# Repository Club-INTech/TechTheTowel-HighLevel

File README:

INTech  2015-2016
In GIT we trust.

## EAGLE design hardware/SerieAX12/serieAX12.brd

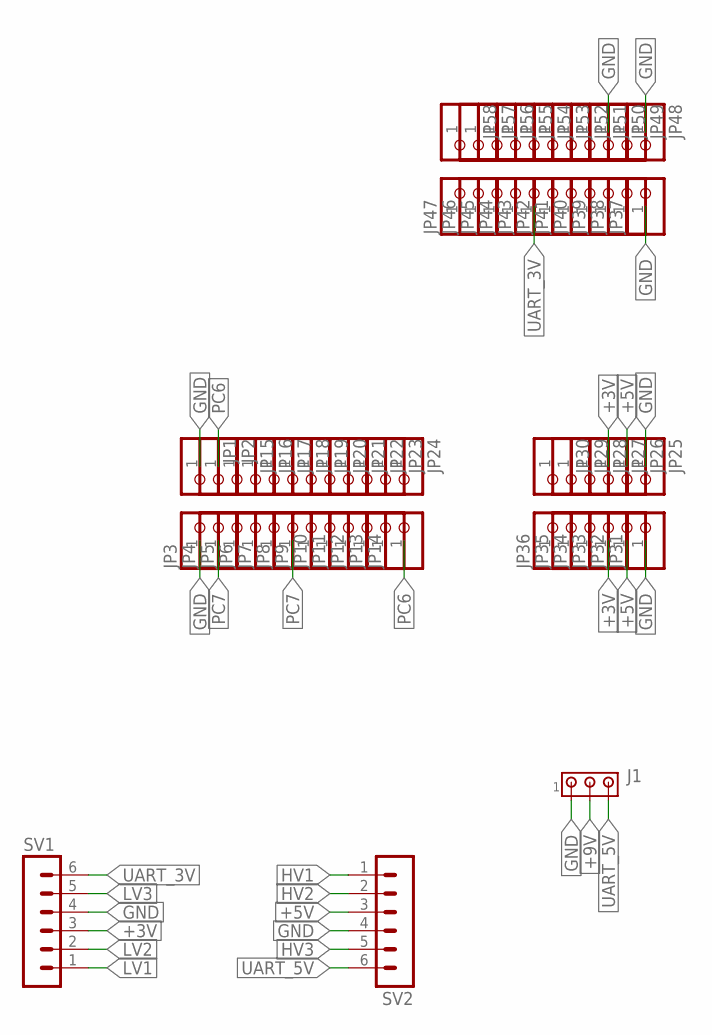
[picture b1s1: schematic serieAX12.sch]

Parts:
J1: MTA03-100; 10X03MTA
JP1, JP2, JP3, JP4, JP5, JP6, JP7, JP8, JP9, JP10, JP11, JP12, JP13, JP14, JP15, JP16, JP17, JP18, JP19, JP20, JP21, JP22, JP23, JP24, JP25, JP26, JP27, JP28, JP29, JP30, JP31, JP32, JP33, JP34, JP35, JP36, JP37, JP38, JP39, JP40, JP41, JP42, JP43, JP44, JP45, JP46, JP47, JP48, JP49, JP50, JP51, JP52, JP53, JP54, JP55, JP56, JP57, JP58: PINHD-1X1; 1X01
SV1, SV2: MA06-1

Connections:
+3V: JP27.1, JP33.1, SV1.3
+5V: JP26.1, JP32.1, SV2.3
+9V: J1.2
GND: J1.1, JP1.1, JP3.1, JP25.1, JP31.1, JP37.1, JP48.1, JP50.1, SV1.4, SV2.4
HV1: SV2.1
HV2: SV2.2
HV3: SV2.5
LV1: SV1.1
LV2: SV1.2
LV3: SV1.5
PC6: JP2.1, JP14.1
PC7: JP4.1, JP8.1
UART_3V: JP43.1, SV1.6
UART_5V: J1.3, SV2.6

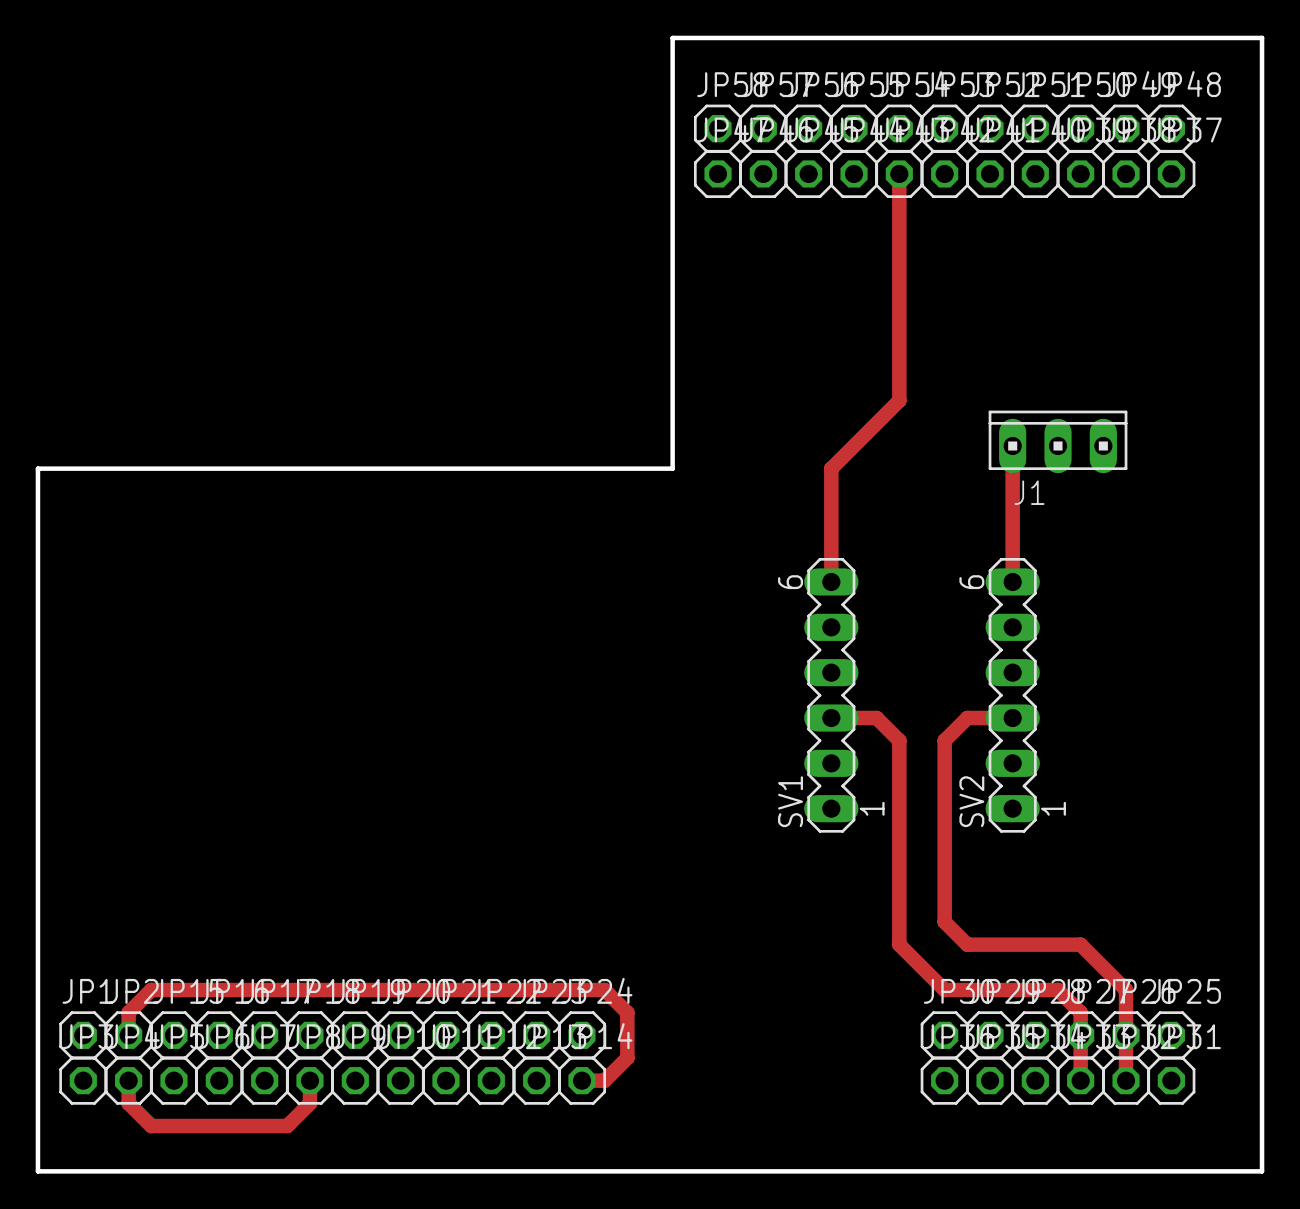
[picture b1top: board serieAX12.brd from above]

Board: 2 copper layers, 68.6 x 63.5 mm, 61 parts (0 on the bottom side), 7 nets.

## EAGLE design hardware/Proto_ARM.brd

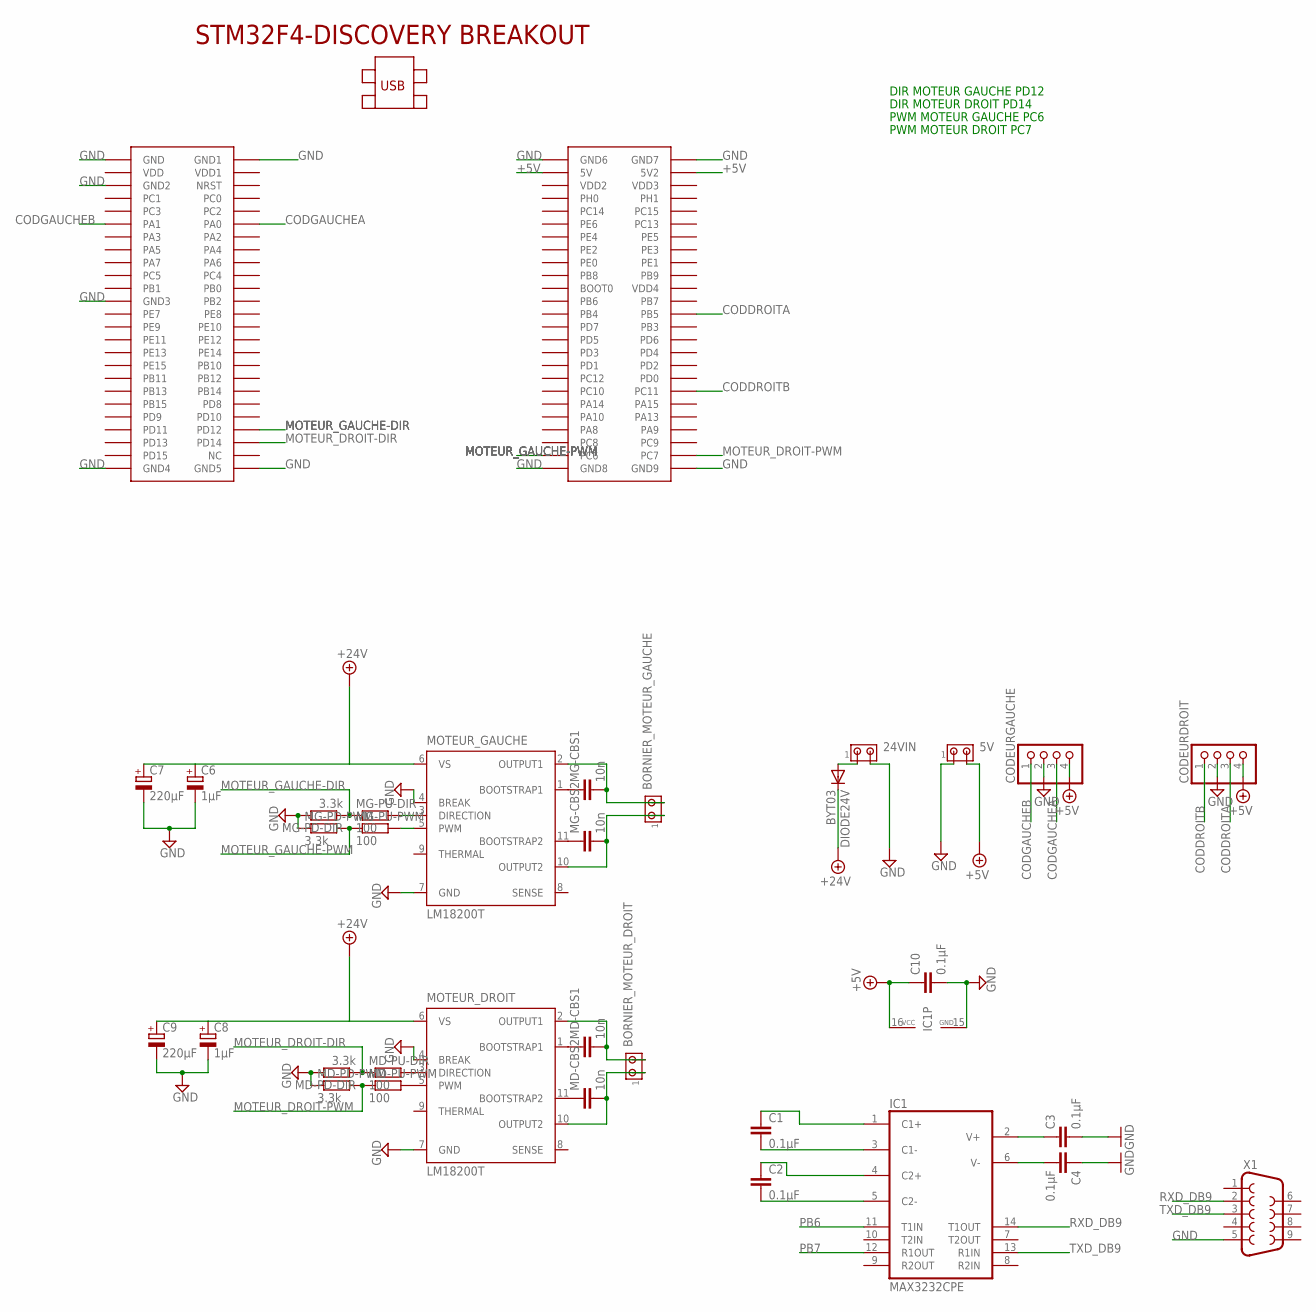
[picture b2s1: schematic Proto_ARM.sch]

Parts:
5V, 24VIN: MTA02-156; 1X2MTA
BORNIER_MOTEUR_DROIT: MTA02-156; 1X2MTA
BORNIER_MOTEUR_GAUCHE: MTA02-156; 1X2MTA
C1, C2, C3, C4, C10: 0.1µF; C050-035X075
C6, C8: 1µF; E3,5-8
C7, C9: 220µF; E3,5-8
CODEURDROIT: PINHD-1X4; 1X04
CODEURGAUCHE: PINHD-1X4; 1X04
DIODE24V: BYT03; DO27-15
IC1: MAX3232CPE; DIL16; MPN MAX3232CPE+
MD-CBS1, MD-CBS2: 10n; C050-025X075
MD-PD-DIR: 3.3k; 0207/7
MD-PD-PWM: 3.3k; 0207/7
MD-PU-DIR: 100; 0207/7
MD-PU-PWM: 100; 0207/7
MG-CBS1, MG-CBS2: 10n; C050-025X075
MG-PD-DIR: 3.3k; 0207/7
MG-PD-PWM: 3.3k; 0207/7
MG-PU-DIR: 100; 0207/7
MG-PU-PWM: 100; 0207/7
MOTEUR_DROIT: LM18200T; TO-220-11
MOTEUR_GAUCHE: LM18200T; TO-220-11
U$1: STM32F4-DISCOVERY
X1: F09HP

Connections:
+5V: 5V.2, C10.1, CODEURDROIT.4, CODEURGAUCHE.4, IC1.16 (VCC), U$1.P$53 (5V), U$1.P$54 (5V2)
+24V: C6.+, C7.+, C8.+, C9.+, DIODE24V.C, MOTEUR_DROIT.6 (VS), MOTEUR_GAUCHE.6 (VS)
CODDROITA: CODEURDROIT.3, U$1.P$76 (PB5)
CODDROITB: CODEURDROIT.1, U$1.P$88 (PC11)
CODGAUCHEA: CODEURGAUCHE.3, U$1.P$12 (PA0)
CODGAUCHEB: CODEURGAUCHE.1, U$1.P$11 (PA1)
GND: 5V.1, 24VIN.2, C3.2, C4.1, C6.-, C7.-, C8.-, C9.-, C10.2, CODEURDROIT.2, CODEURGAUCHE.2, IC1.15 (GND), MD-PD-DIR.2, MD-PD-PWM.1, MG-PD-DIR.2, MG-PD-PWM.1, MOTEUR_DROIT.4 (BREAK), MOTEUR_DROIT.7 (GND), MOTEUR_GAUCHE.4 (BREAK), MOTEUR_GAUCHE.7 (GND), U$1.P$1 (GND), U$1.P$2 (GND1), U$1.P$5 (GND2), U$1.P$23 (GND3), U$1.P$49 (GND4), U$1.P$50 (GND5), U$1.P$51 (GND6), U$1.P$52 (GND7), U$1.P$99 (GND8), U$1.P$100 (GND9), X1.5
MOTEUR_DROIT-DIR: MD-PD-DIR.1, MD-PU-DIR.1, U$1.P$46 (PD14)
MOTEUR_DROIT-PWM: MD-PD-PWM.2, MD-PU-PWM.1, U$1.P$98 (PC7)
MOTEUR_GAUCHE-DIR: MG-PD-DIR.1, MG-PU-DIR.1, U$1.P$44 (PD12)
MOTEUR_GAUCHE-PWM: MG-PD-PWM.2, MG-PU-PWM.1, U$1.P$97 (PC6)
unnamed: C1.1, IC1.1 (C1+)
unnamed: MG-CBS1.1, MOTEUR_GAUCHE.1 (BOOTSTRAP1)
unnamed: MG-CBS2.1, MOTEUR_GAUCHE.11 (BOOTSTRAP2)
unnamed: MD-CBS2.1, MOTEUR_DROIT.11 (BOOTSTRAP2)
unnamed: MD-CBS1.1, MOTEUR_DROIT.1 (BOOTSTRAP1)
unnamed: BORNIER_MOTEUR_DROIT.2, MD-CBS1.2, MOTEUR_DROIT.2 (OUTPUT1)
unnamed: BORNIER_MOTEUR_DROIT.1, MD-CBS2.2, MOTEUR_DROIT.10 (OUTPUT2)
unnamed: BORNIER_MOTEUR_GAUCHE.1, MG-CBS2.2, MOTEUR_GAUCHE.10 (OUTPUT2)
unnamed: BORNIER_MOTEUR_GAUCHE.2, MG-CBS1.2, MOTEUR_GAUCHE.2 (OUTPUT1)
unnamed: C4.2, IC1.6 (V-)
unnamed: MG-PU-DIR.2, MOTEUR_GAUCHE.3 (DIRECTION)
unnamed: MG-PU-PWM.2, MOTEUR_GAUCHE.5 (PWM)
unnamed: MD-PU-DIR.2, MOTEUR_DROIT.3 (DIRECTION)
unnamed: MD-PU-PWM.2, MOTEUR_DROIT.5 (PWM)
unnamed: C3.1, IC1.2 (V+)
unnamed: C1.2, IC1.3 (C1-)
unnamed: 24VIN.1, DIODE24V.A
unnamed: C2.1, IC1.4 (C2+)
unnamed: C2.2, IC1.5 (C2-)
PB6: IC1.11 (T1IN)
PB7: IC1.12 (R1OUT)
RXD_DB9: IC1.14 (T1OUT), X1.2
TXD_DB9: IC1.13 (R1IN), X1.3

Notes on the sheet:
DIR MOTEUR GAUCHE PD12
DIR MOTEUR DROIT PD14
PWM MOTEUR GAUCHE PC6
PWM MOTEUR DROIT PC7

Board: 2 copper layers, 33 parts (0 on the bottom side), 32 nets, no tracks yet.

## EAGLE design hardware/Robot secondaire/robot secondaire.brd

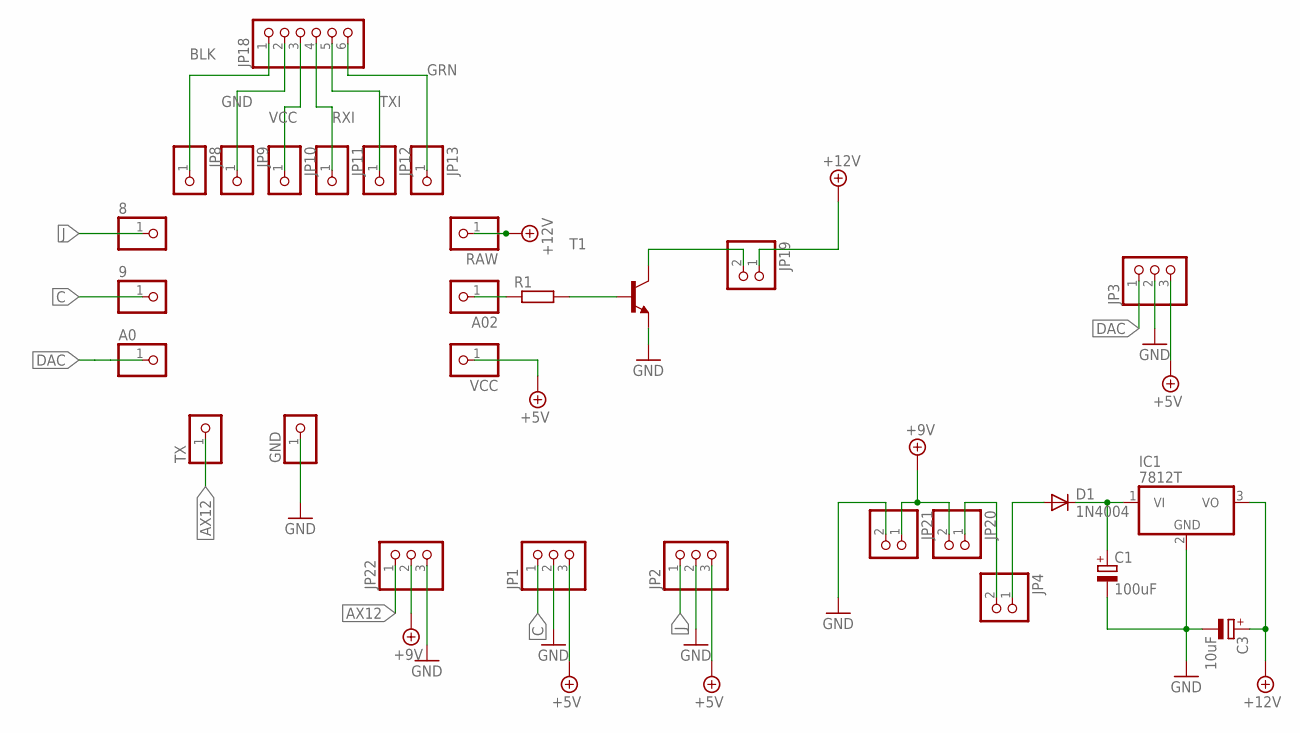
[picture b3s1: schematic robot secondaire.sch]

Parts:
8, 9: PINHD-1X1; 1X01
A0, A02: PINHD-1X1; 1X01
C1: 100uF; E3,5-10
C3: 10uF; E2,5-6E
D1: 1N4004; DO41-10
GND: PINHD-1X1; 1X01
IC1: 7812T; TO220H
JP1, JP2, JP3, JP22: PINHD-1X3; 1X03
JP4, JP19, JP20, JP21: PINHD-1X2; 1X02
JP8, JP9, JP10, JP11, JP12, JP13: PINHD-1X1; 1X01
JP18: PINHD-1X6; 1X06
R1: R-EU_0204/7; 0204/7
RAW: PINHD-1X1; 1X01
T1: 2N4124-NPN-TO92-CBE; TO92-CBE
TX: PINHD-1X1; 1X01
VCC: PINHD-1X1; 1X01

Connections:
+5V: JP1.3, JP2.3, JP3.3, VCC.1
+9V: JP20.2, JP21.1, JP22.2
+12V: C3.+, IC1.3 (VO), JP19.1, RAW.1
AX12: JP22.1, TX.1
BLK: JP8.1, JP18.1
C: 9.1, JP1.1
CMD_MOTEUR: A02.1, R1.1
DAC: A0.1, JP3.1
GND: C1.-, C3.-, GND.1, IC1.2 (GND), JP1.2, JP2.2, JP3.2, JP9.1, JP18.2, JP21.2, JP22.3, T1.E
GRN: JP13.1, JP18.6
J: 8.1, JP2.1
unnamed: C1.+, D1.C, IC1.1 (VI)
unnamed: D1.A, JP4.1
unnamed: JP4.2, JP20.1
unnamed: R1.2, T1.B
unnamed: JP19.2, T1.C
RXI: JP11.1, JP18.4
TXI: JP12.1, JP18.5
VCC: JP10.1, JP18.3

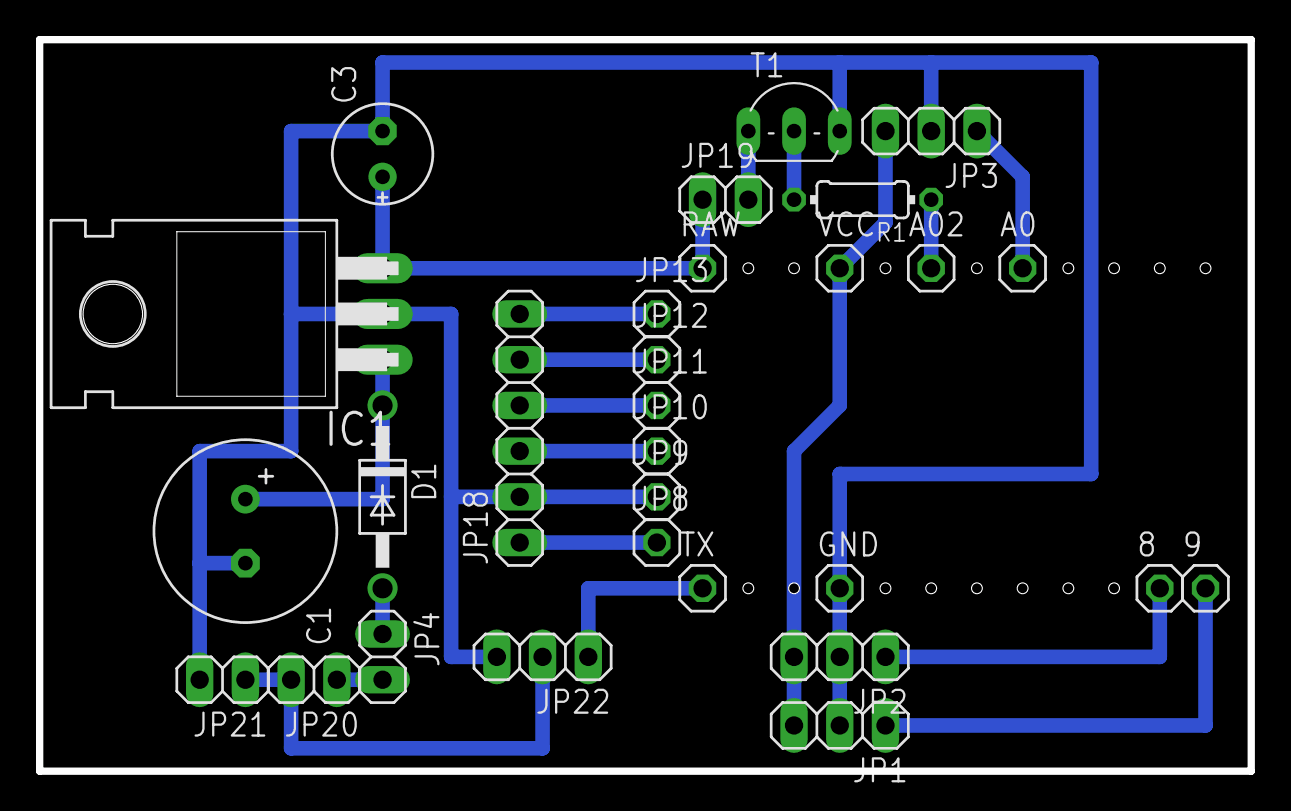
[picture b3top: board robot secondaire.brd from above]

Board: 2 copper layers, 67.3 x 40.6 mm, 29 parts (0 on the bottom side), 19 nets.

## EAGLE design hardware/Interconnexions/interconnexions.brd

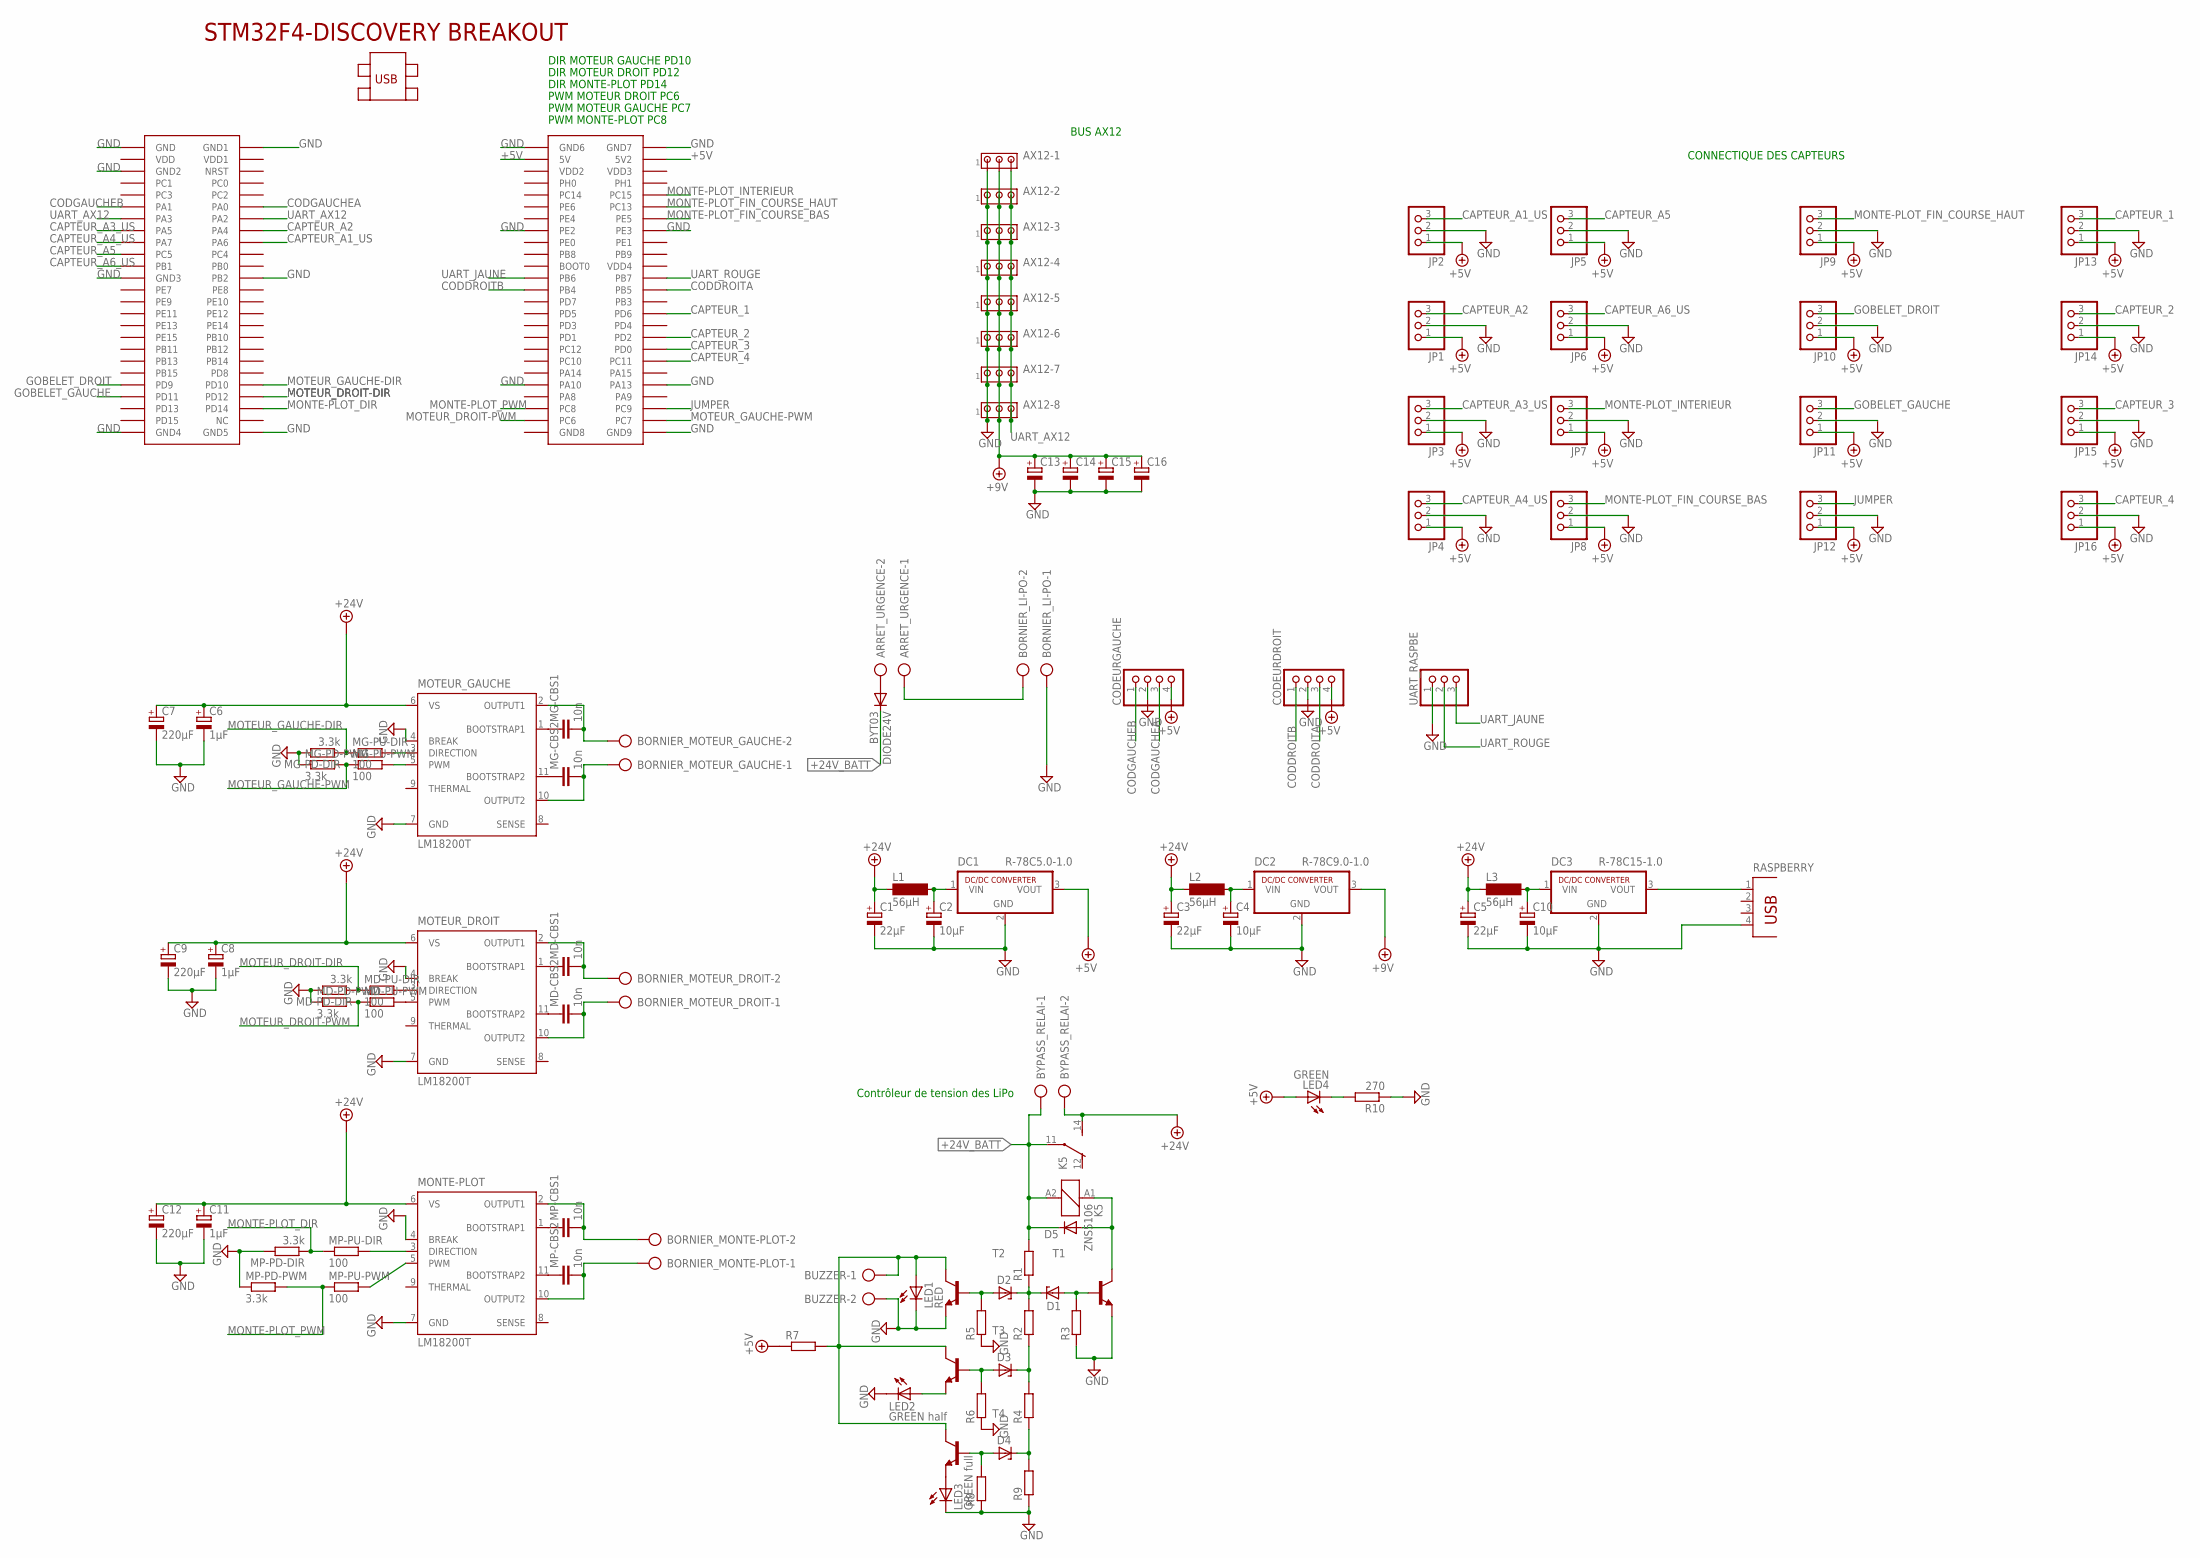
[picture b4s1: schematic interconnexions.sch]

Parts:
ARRET_URGENCE: AK300/2
AX12-1, AX12-2, AX12-3, AX12-4, AX12-5, AX12-6, AX12-7, AX12-8: MTA03-100; 10X03MTA
BORNIER_LI-PO: AK300/2
BORNIER_MONTE-PLOT: AK300/2
BORNIER_MOTEUR_DROIT: AK300/2
BORNIER_MOTEUR_GAUCHE: AK300/2
BUZZER: AK300/2
BYPASS_RELAI: AK300/2
C1, C3, C5: 22µF; E2,5-6E
C2, C4, C10: 10µF; E2,5-6E
C6, C8, C11: 1µF; E3,5-8
C7, C9, C12: 220µF; E3,5-8
C13, C14, C15, C16: CPOL-EUE2,5-6E; E2,5-6E
CODEURDROIT: PINHD-1X4; 1X04
CODEURGAUCHE: PINHD-1X4; 1X04
D1, D2, D3, D4: ZENER-DIODEZD-2.5; ZDIO-2.5
D5: DIODE-D-2.5; D-2.5
DC1: R-78C5.0-1.0; SIP3
DC2: R-78C9.0-1.0; SIP3
DC3: R-78C15-1.0; SIP3
DIODE24V: BYT03; DO27-15
JP1, JP2, JP3, JP4, JP5, JP6, JP7, JP8, JP9, JP10, JP11, JP12, JP13, JP14, JP15, JP16: PINHD-1X3; 1X03
K5: ZNS5106; ZN5
L1, L2, L3: 56µH; SD12K100
LED1: RED; LED5MM
LED2: GREEN half; LED5MM
LED3: GREEN full; LED5MM
LED4: GREEN; LED5MM
MD-CBS1, MD-CBS2: 10n; C050-025X075
MD-PD-DIR: 3.3k; 0207/10
MD-PD-PWM: 3.3k; 0207/7
MD-PU-DIR: 100; 0207/7
MD-PU-PWM: 100; 0207/15
MG-CBS1, MG-CBS2: 10n; C050-025X075
MG-PD-DIR: 3.3k; 0207/7
MG-PD-PWM: 3.3k; 0207/7
MG-PU-DIR: 100; 0207/7
MG-PU-PWM: 100; 0207/15
MONTE-PLOT: LM18200T; TO-220-11
MOTEUR_DROIT: LM18200T; TO-220-11
MOTEUR_GAUCHE: LM18200T; TO-220-11
MP-CBS1, MP-CBS2: 10n; C050-025X075
MP-PD-DIR: 3.3k; 0207/10
MP-PD-PWM: 3.3k; 0207/7
MP-PU-DIR: 100; 0207/7
MP-PU-PWM: 100; 0207/15
R1, R3, R5, R6: R-EU_0207/2V; 0207/2V
R2, R4, R7, R9: R-EU_0204/7; 0204/7
R8: R-EU_0204/5; 0204/5
R10: 270; 0207/2V
RASPBERRY: PN87520
T1, T2, T3, T4: 2N5400-NPN-TO92-CBE; TO92-CBE
U$1: STM32F4-DISCOVERY
UART_RASPBE: PINHD-1X3; 1X03

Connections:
+5V: CODEURDROIT.4, CODEURGAUCHE.4, DC1.3 (VOUT), JP1.1, JP2.1, JP3.1, JP4.1, JP5.1, JP6.1, JP7.1, JP8.1, JP9.1, JP10.1, JP11.1, JP12.1, JP13.1, JP14.1, JP15.1, JP16.1, LED4.A, R7.1, U$1.P$53 (5V), U$1.P$54 (5V2)
+9V: AX12-1.2, AX12-2.2, AX12-3.2, AX12-4.2, AX12-5.2, AX12-6.2, AX12-7.2, AX12-8.2, C13.+, C14.+, C15.+, C16.+, DC2.3 (VOUT)
+15V: DC3.3 (VOUT), RASPBERRY.1
+24V: BYPASS_RELAI.2, C1.+, C3.+, C5.+, C6.+, C7.+, C8.+, C9.+, C11.+, C12.+, K5.14 (S), L1.1, L2.1, L3.1, MONTE-PLOT.6 (VS), MOTEUR_DROIT.6 (VS), MOTEUR_GAUCHE.6 (VS)
+24V_BATT: BYPASS_RELAI.1, D5.C, DIODE24V.C, K5.11, K5.A2 (2), R1.2
CAPTEUR_1: JP16.3, U$1.P$88 (PC11)
CAPTEUR_2: JP15.3, U$1.P$86 (PD0)
CAPTEUR_3: JP14.3, U$1.P$84 (PD2)
CAPTEUR_4: JP13.3, U$1.P$80 (PD6)
CAPTEUR_A1: JP5.3, U$1.P$19 (PC5)
CAPTEUR_A2: JP3.3, U$1.P$15 (PA5)
CAPTEUR_US_AR_D: JP4.3, U$1.P$17 (PA7)
CAPTEUR_US_AR_G: JP6.3, U$1.P$21 (PB1)
CAPTEUR_US_AV_D: JP2.3, U$1.P$18 (PA6)
CAPTEUR_US_AV_G: JP1.3, U$1.P$16 (PA4)
CODDROITA: CODEURDROIT.3, U$1.P$76 (PB5)
CODDROITB: CODEURDROIT.1, U$1.P$75 (PB4)
CODGAUCHEA: CODEURGAUCHE.3, U$1.P$12 (PA0)
CODGAUCHEB: CODEURGAUCHE.1, U$1.P$11 (PA1)
GND: AX12-1.1, AX12-2.1, AX12-3.1, AX12-4.1, AX12-5.1, AX12-6.1, AX12-7.1, AX12-8.1, BORNIER_LI-PO.1, BUZZER.2, C1.-, C2.-, C3.-, C4.-, C5.-, C6.-, C7.-, C8.-, C9.-, C10.-, C11.-, C12.-, C13.-, C14.-, C15.-, C16.-, CODEURDROIT.2, CODEURGAUCHE.2, DC1.2 (GND), DC2.2 (GND), DC3.2 (GND), JP1.2, JP2.2, JP3.2, JP4.2, JP5.2, JP6.2, JP7.2, JP8.2, JP9.2, JP10.2, JP11.2, JP12.2, JP13.2, JP14.2, JP15.2, JP16.2, LED1.K (C), LED2.K (C), LED3.K (C), MD-PD-DIR.2, MD-PD-PWM.1, MG-PD-DIR.2, MG-PD-PWM.1, MONTE-PLOT.4 (BREAK), MONTE-PLOT.7 (GND), MOTEUR_DROIT.4 (BREAK), MOTEUR_DROIT.7 (GND), MOTEUR_GAUCHE.4 (BREAK), MOTEUR_GAUCHE.7 (GND), MP-PD-DIR.2, MP-PD-PWM.1, R3.1, R5.1, R6.1, R8.1, R9.1, R10.1, RASPBERRY.4, T1.E, T2.E, U$1.P$1 (GND), U$1.P$2 (GND1), U$1.P$5 (GND2), U$1.P$23 (GND3), U$1.P$24 (PB2), U$1.P$49 (GND4), U$1.P$50 (GND5), U$1.P$51 (GND6), U$1.P$52 (GND7), U$1.P$65 (PE2), U$1.P$66 (PE3), U$1.P$91 (PA10), U$1.P$92 (PA13), U$1.P$100 (GND9), UART_RASPBE.1
GOBELET_DROIT: JP10.3, U$1.P$41 (PD9)
GOBELET_GAUCHE: JP11.3, U$1.P$43 (PD11)
JUMPER: JP12.3, U$1.P$96 (PC9)
MONTE-PLOT_DIR: MP-PD-DIR.1, MP-PU-DIR.1, U$1.P$46 (PD14)
MONTE-PLOT_FIN_COURSE_BAS: JP8.3, U$1.P$64 (PE5)
MONTE-PLOT_FIN_COURSE_HAUT: JP9.3, U$1.P$62 (PC13)
MONTE-PLOT_INTERIEUR: JP7.3, U$1.P$60 (PC15)
MONTE-PLOT_PWM: MP-PD-PWM.2, MP-PU-PWM.1, U$1.P$95 (PC8)
MOTEUR_DROIT-DIR: MD-PD-DIR.1, MD-PU-DIR.1, U$1.P$44 (PD12)
MOTEUR_DROIT-PWM: MD-PD-PWM.2, MD-PU-PWM.1, U$1.P$97 (PC6)
MOTEUR_GAUCHE-DIR: MG-PD-DIR.1, MG-PU-DIR.1, U$1.P$42 (PD10)
MOTEUR_GAUCHE-PWM: MG-PD-PWM.2, MG-PU-PWM.1, U$1.P$98 (PC7)
unnamed: C2.+, DC1.1 (VIN), L1.2
unnamed: C4.+, DC2.1 (VIN), L2.2
unnamed: C10.+, DC3.1 (VIN), L3.2
unnamed: MONTE-PLOT.1 (BOOTSTRAP1), MP-CBS1.1
unnamed: MG-CBS1.1, MOTEUR_GAUCHE.1 (BOOTSTRAP1)
unnamed: MG-CBS2.1, MOTEUR_GAUCHE.11 (BOOTSTRAP2)
unnamed: MD-CBS2.1, MOTEUR_DROIT.11 (BOOTSTRAP2)
unnamed: MD-CBS1.1, MOTEUR_DROIT.1 (BOOTSTRAP1)
unnamed: BORNIER_MOTEUR_DROIT.2, MD-CBS1.2, MOTEUR_DROIT.2 (OUTPUT1)
unnamed: BORNIER_MOTEUR_DROIT.1, MD-CBS2.2, MOTEUR_DROIT.10 (OUTPUT2)
unnamed: BORNIER_MOTEUR_GAUCHE.1, MG-CBS2.2, MOTEUR_GAUCHE.10 (OUTPUT2)
unnamed: BORNIER_MOTEUR_GAUCHE.2, MG-CBS1.2, MOTEUR_GAUCHE.2 (OUTPUT1)
unnamed: MONTE-PLOT.11 (BOOTSTRAP2), MP-CBS2.1
unnamed: MG-PU-DIR.2, MOTEUR_GAUCHE.3 (DIRECTION)
unnamed: MG-PU-PWM.2, MOTEUR_GAUCHE.5 (PWM)
unnamed: MD-PU-DIR.2, MOTEUR_DROIT.3 (DIRECTION)
unnamed: MD-PU-PWM.2, MOTEUR_DROIT.5 (PWM)
unnamed: BORNIER_MONTE-PLOT.1, MONTE-PLOT.10 (OUTPUT2), MP-CBS2.2
unnamed: BORNIER_MONTE-PLOT.2, MONTE-PLOT.2 (OUTPUT1), MP-CBS1.2
unnamed: MONTE-PLOT.3 (DIRECTION), MP-PU-DIR.2
unnamed: MONTE-PLOT.5 (PWM), MP-PU-PWM.2
unnamed: LED4.K (C), R10.2
unnamed: ARRET_URGENCE.1, BORNIER_LI-PO.2
unnamed: D5.A, K5.A1 (1), T1.C
unnamed: D1.C, D2.C, R1.1, R2.2
unnamed: D1.A, R3.2, T1.B
unnamed: D2.A, R5.2, T2.B
unnamed: BUZZER.1, LED1.A, R7.2, T2.C, T3.C, T4.C
unnamed: D3.C, R2.1, R4.2
unnamed: LED2.A, T3.E
unnamed: D3.A, R6.2, T3.B
unnamed: LED3.A, T4.E
unnamed: D4.C, R4.1, R9.2
unnamed: D4.A, R8.2, T4.B
unnamed: ARRET_URGENCE.2, DIODE24V.A
UART_AX12: AX12-1.3, AX12-2.3, AX12-3.3, AX12-4.3, AX12-5.3, AX12-6.3, AX12-7.3, AX12-8.3, U$1.P$13 (PA3), U$1.P$14 (PA2)
UART_JAUNE: U$1.P$73 (PB6), UART_RASPBE.3
UART_ROUGE: U$1.P$74 (PB7), UART_RASPBE.2

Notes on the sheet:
DIR MOTEUR GAUCHE PD10
DIR MOTEUR DROIT PD12
PWM MOTEUR DROIT PC6
PWM MOTEUR GAUCHE PC7
BUS AX12
CONNECTIQUE DES CAPTEURS
Contrôleur de tension des LiPo
DIR MONTE-PLOT PD14
PWM MONTE-PLOT PC8

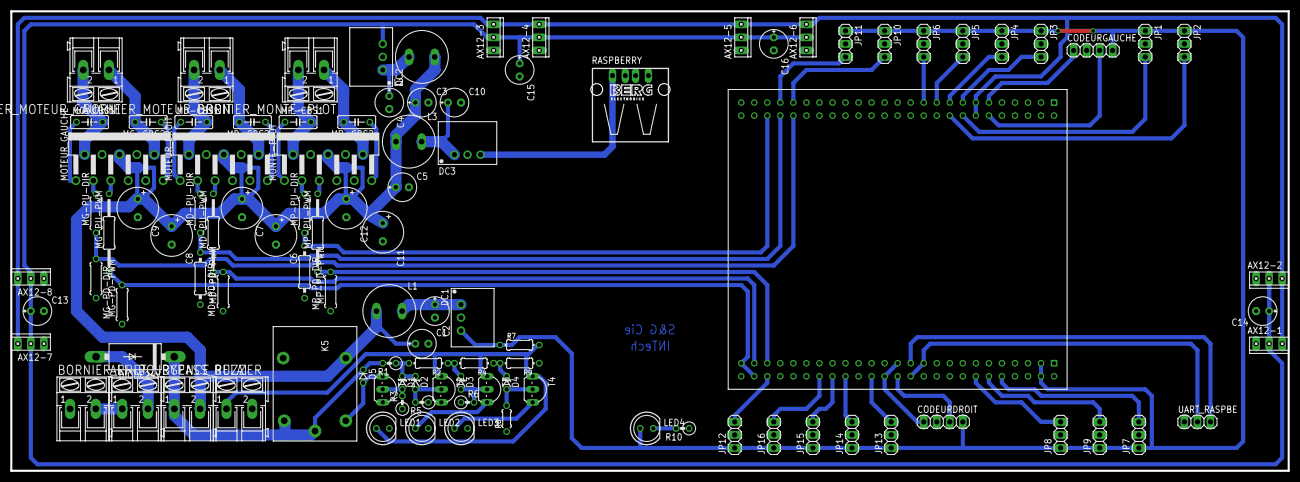
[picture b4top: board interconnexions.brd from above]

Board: 2 copper layers, 248.9 x 89.5 mm, 104 parts (0 on the bottom side), 70 nets.

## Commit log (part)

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2016-04-26 fin d'IA
2016-04-26 rush fishing
2016-04-26 fail boundaries
2016-04-26 modif entryposition de closedoors v3
2016-04-26 ajout d'une pseudo version castle
2016-04-26 detection plus basique dans sable
2016-04-26 fail
2016-04-26 fail du borgne
2016-04-26 fail again
2016-04-26 corrections sable
2016-04-26 marges
2016-04-26 Fail castle
2016-04-26 plus proche
2016-04-26 je ne sais plus me servir de git
2016-04-26 modif fishing et castle
2016-04-26 portes
2016-04-26 no more log after match
2016-04-26 modif finalize fishing et stratégie associée
2016-04-26 fishing vérifie les problèmes de portes bloquées
2016-04-26 corrections
2016-04-26 moins de rayon
2016-04-26 fail2
2016-04-26 fail3
2016-04-26 basic detec fishing
2016-04-26 modif fishing
2016-04-26 modifs entryposition
2016-04-26 diverses correction, NYEH HEH HEH !
2016-04-26 ajout de debug dans fishing et entryposition de castle
2016-04-26 merge
2016-04-26 fail doors
2016-04-26 shellgetter en basic
2016-04-26 marge
2016-04-26 modif de fishing en cas d'obstacle
2016-04-26 jean-michou
2016-04-26 probe
2016-04-26 probe2
2016-04-26 fail shells corrigé
2016-04-26 modif de disengage
2016-04-26 modif de disengage, sengage
2016-04-26 failsafe forced
2016-04-26 modif fishing blocage filet
2016-04-26 priorités threads
2016-04-26 modif fishing, c'est le dawa !
2016-04-26 ouverture porte castle[C
2016-04-26 fermeture prématurée
2016-04-26 modif fishing, again
2016-04-26 That was at this momen that CF knew... he evolved into CF2 !
2016-04-26 modif fishing en cas d'obstacle
2016-04-26 corrections rayon
2016-04-26 petit oubli
2016-04-26 basic is love, basic is life
2016-04-26 hook de vitesse
2016-04-26 clean af
2016-04-27 disengage par arc
2016-04-27 disengage par arc fiable
2016-04-27 degagement sable si ennemi
2016-04-27 modif disengage par arc au niveau du fishing
2016-04-27 hook de sable
2016-04-27 #basicForTheWin
2016-04-27 #fail
2016-04-27 modif disengage arc pour close doors
2016-04-27 homo
2016-04-27 homo++
2016-04-27 homo--
2016-04-27 homo OK
2016-04-27 tech
2016-04-27 tech2
2016-04-27 fishing v4 fait un aller de plus
2016-04-27 rectif fishing
2016-04-27 shells + sortie tech
2016-04-27 shells junit
2016-04-27 shutdown serie
2016-04-27 shell slowdown
2016-04-27 modif fishing en cas de blocage
2016-04-27 fishing junit
2016-04-28 debug
2016-04-28 fail flush
2016-04-28 no more debug
2016-04-28 recul
2016-04-28 valeurs
2016-04-28 clear des hooks en cas de blocage dans le fishing
2016-04-28 recule pas
2016-04-28 oubli de booléen dans fishing
2016-04-28 recalage x
2016-04-28 ajout de log
2016-04-28 hook de repo
2016-04-28 rapide modif
2016-04-28 anims
2016-04-28 shell getter un peu moins loin
2016-04-28 rename des anims
2016-04-28 ajout d'anim yeux
2016-04-28 on ne se recale plus
2016-04-28 intégration yeux
2016-04-28 ajout choquée
2016-04-28 jsuis choque
2016-04-28 jsuis encore choque
2016-04-28 new serial
2016-04-28 changement
2016-04-28 desespoir
2016-04-28 meilleure gestion d'exception pour fishing
2016-04-29 revert shells
2016-04-29 revert du revert du recalage
2016-04-29 timeout pour readline
2016-04-29 fail log
2016-04-29 test
2016-04-29 Je fais joujou avec les yeux. Bite.
2016-04-29 correction des fichiers tiles
2016-04-29 re modif des tiles
2016-04-29 Bite.
2016-04-29 Bite3.
2016-04-29 Oh Tintin, vous etes un ananas !
2016-04-29 Le problème du temps, c'est un non problème !
2016-04-29 Un original ! quelle chance !
2016-04-29 j'aaaariiiiiiiveee
2016-04-29 Je me sens, comme une bamba triste !
2016-04-29 les ; c'est pas surfait...
2016-04-29 enregistrement des pos
2016-04-29 meilleur rayon cod + système anti-recalement si cylindre
2016-04-29 plus d'attente pour le magnet down
2016-04-29 modif des expectedwallimpact dans fishing
2016-04-29 adieu fushing par arc
2016-04-29 et son Junit
2016-04-29 jars
2016-04-29 modifs fishing
2016-04-29 no more shells
2016-04-29 slow down fishing + techthesand on tourne moins loin
2016-04-29 fail fishing
2016-04-29 slow down sable
2016-04-29 slooooowwww
2016-04-29 un poil plus vite
2016-04-30 no more rush with sand
2016-04-30 un peu plus doucement pour l'entrée dans le sable
2016-04-30 new position
2016-04-30 on pousse plus loin
2016-04-30 on detecte pas au MAUVAIS MOMENT
2016-04-30 un peu moins loin
2016-04-30 on va un peu plus vite et fishing va un peu plus proche
2016-04-30 ou pas, j'ai rien dit
2016-04-30 double axis for double fun !
2016-04-30 quatrième passage dans fishing
2016-04-30 debug serie
2016-04-30 new systeme d'acquittement
2016-04-30 recalage forcé
2016-04-30 modif hook dernier passage fishing
2016-04-30 Ne sait pas utiliser un PDD
2016-04-30 créneau plus loin
2016-05-01 recalage angulaire portes
2016-05-01 fishing plus rapide et créneau plus loin
2016-05-01 fishing créneau
2016-05-01 hook
2016-05-01 modif again
2016-05-01 again
2016-05-01 fishing avec arc
2016-05-01 fishing avec arc FIN !
2016-05-01 fishing avec arc FIN DE VRAI!
2016-05-01 modif arc fishing
2016-05-01 modif netPos
2016-05-01 moins de blocage sable + forcing portes
2016-05-01 fail force
2016-05-01 un peu moins long
2016-05-01 meilleure gestion du forcing
2016-05-01 meilleure gestion du forcing 2
2016-05-01 rayon un poil plus élevé
2016-05-01 homo plus précis
2016-05-01 modif fishing v4 expérimental
2016-05-01 junit fishing
2016-05-01 fishingv4 rayon cb +2cm
2016-05-01 fishingv4
2016-05-01 fishingv4 recul en medium
2016-05-01 no detection turn sand
2016-05-01 no forcing sand
2016-05-01 sand
2016-05-01 MoveArcWithNoDetectionWhileTurningForGoodAngle
2016-05-01 mode borgne jusqu'au bout (de la nuit)
2016-05-01 no more retry
2016-05-01 no more secret feature
2016-05-01 revert
2016-05-02 readLine moins lourd sur le CPU + gain de temps dans le PDD par un thread de travail
2016-05-02 Ajout massif de log dans fishing v4
2016-05-02 ThreadWorker OK
2016-05-02 modif fishing et disengage
2016-05-02 multiples corrections IA
2016-05-02 un peu plus à gauche pour les portes
2016-05-02 entrée courbe en expected wall impact
2016-05-02 idem sortie
2016-05-02 no more robotchrono
2016-05-02 un poil plus bourrin
2016-05-02 fast mudafuka
2016-05-02 leger decalage
2016-05-02 multiples corrections
2016-05-02 plus loin
2016-05-02 modif de booléen hors de table
2016-05-02 moins loin
2016-05-02 capteurs
2016-05-02 no more double sym
2016-05-02 techthesand sym
2016-05-03 distance de detection basique dans config + correction priorité ThreadWorker
2016-05-03 petit clean !
2016-05-03 NYEH HEH HEH
2016-05-03 fail copy arc
2016-05-03 Sécurisation fishing porte + passage supplémentaire
2016-05-03 corrections fishing
2016-05-03 refactor....
2016-05-03 opti fishing
2016-05-03 opti castle
2016-05-03 construction du graphe pré-match
2016-05-03 degagement fishing un peu moins loin
2016-05-03 fuck
2016-05-03 forcing x
2016-05-03 basic
2016-05-03 opti
2016-05-04 FUCCKK
2016-05-04 arc en try fishing + tech un peu plus loin 2cm
2016-05-04 on recule avnt de trouner
2016-05-04 homologation
2016-05-04 BOURRRRIIIINNNNN
2016-05-04 correction
2016-05-04 safe turn
2016-05-04 corr
2016-05-05 premier build stratégique
2016-05-05 positions fishing
2016-05-05 corrections + script 3 techthesand
2016-05-05 correctionsd
2016-05-06 passages
2016-05-07 tentative
2016-05-11 too bad bro
2016-06-07 borne arcade
2016-06-07 inver
2016-06-08 middle
2016-06-16 Fail, refeactor de nouveau
2016-06-16 refail
2016-06-30 meilleure gestion création d'arcs
2016-07-14 Passage au serialWrapper
2016-07-14 a pu avr
2016-07-23 a pu traj courbes
2016-07-23 multi-canal
2016-07-23 datahndler
2016-07-23 eventhandler
2016-07-24 debug LL !
2016-07-24 Un robot unique pour les gouverner tous !
2016-07-24 Clean
2016-07-24 Threading ok
2017-03-21 Create LICENSE
